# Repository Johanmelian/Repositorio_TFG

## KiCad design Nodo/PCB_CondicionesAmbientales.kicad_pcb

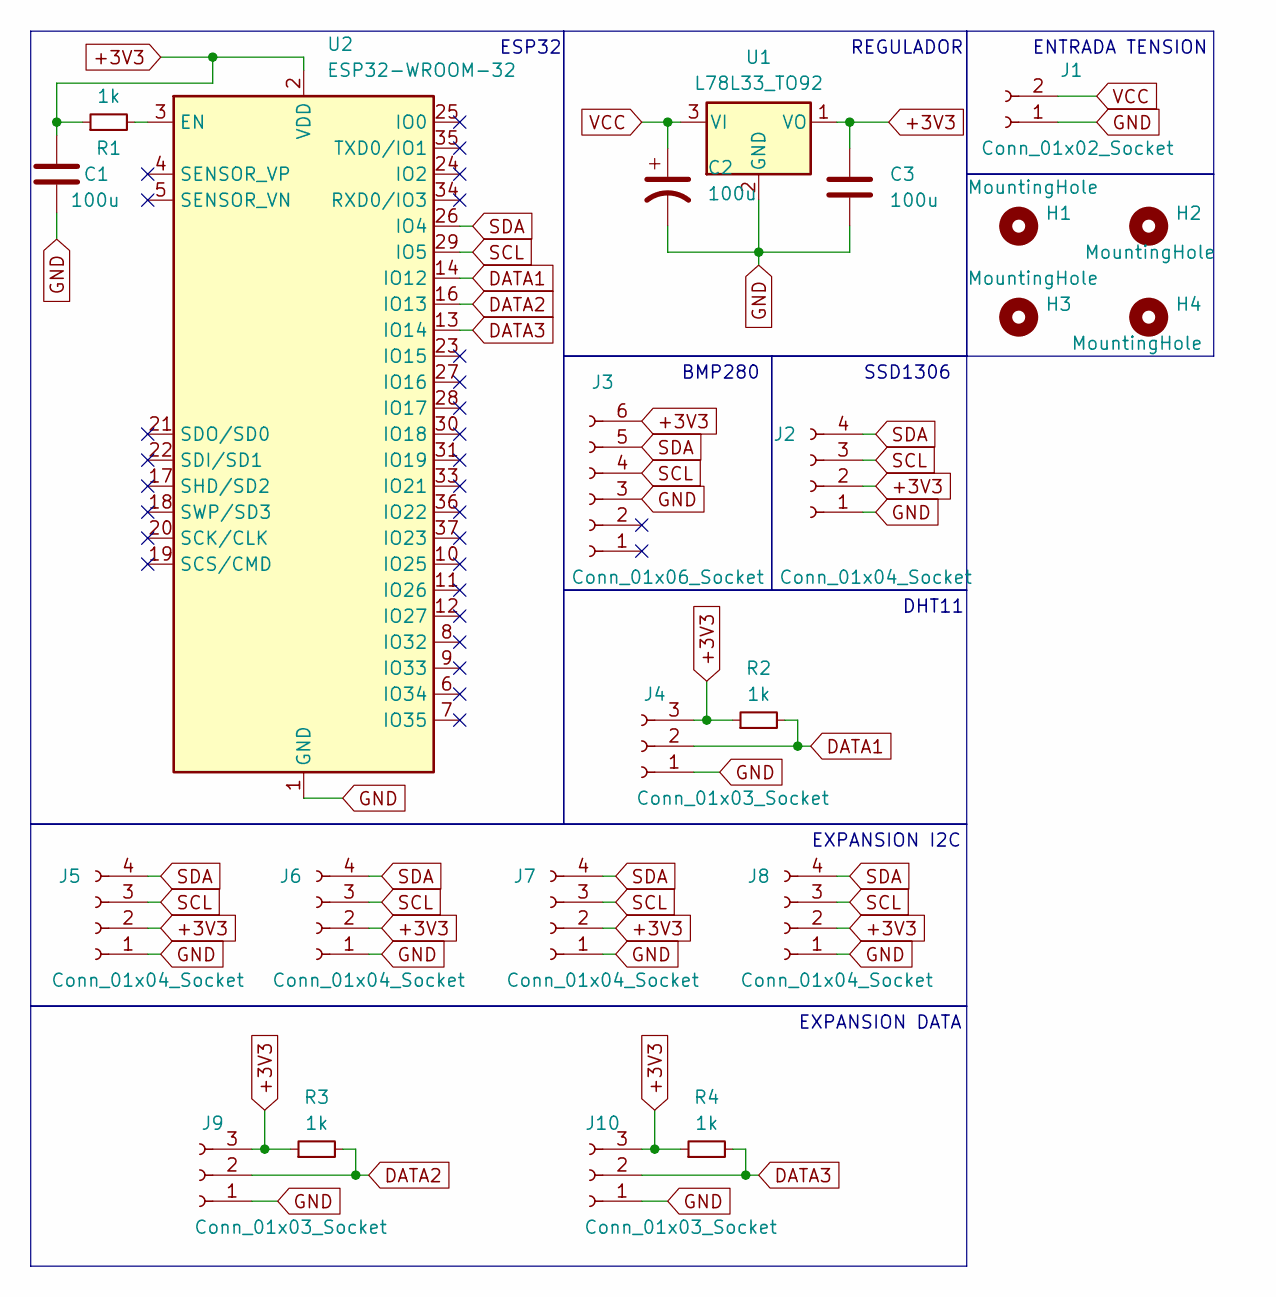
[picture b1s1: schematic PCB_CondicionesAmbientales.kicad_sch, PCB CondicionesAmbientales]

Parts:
C1, C2, C3: 100u; C_Radial_D6.3mm_H5.0mm_P2.50mm
H1, H2, H3, H4: MountingHole; MountingHole_2.5mm
J1: Conn_01x02_Socket; PinSocket_1x02_P2.54mm_Vertical
J2, J5, J6, J7, J8: Conn_01x04_Socket; PinSocket_1x04_P2.54mm_Vertical
J3: Conn_01x06_Socket; PinSocket_1x06_P2.54mm_Vertical
J4, J9, J10: Conn_01x03_Socket; PinSocket_1x03_P2.54mm_Vertical
R1, R2, R3, R4: 1k; R_Axial_DIN0204_L3.6mm_D1.6mm_P7.62mm_Horizontal
U1: L78L33_TO92; TO-92_Inline
U2: ESP32-WROOM-32

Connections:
+3V3: C1.1, C3.1, J2.2, J3.6, J4.3, J5.2, J6.2, J7.2, J8.2, J9.3, J10.3, R1.1, R2.1, R3.1, R4.1, U1.1 (VO), U2.2 (VDD)
DATA1: J4.2, R2.2, U2.14 (IO12)
DATA2: J9.2, R3.2, U2.16 (IO13)
DATA3: J10.2, R4.2, U2.13 (IO14)
GND: C1.2, C2.2, C3.2, J1.1, J2.1, J3.3, J4.1, J5.1, J6.1, J7.1, J8.1, J9.1, J10.1, U1.2 (GND), U2.1 (GND), U2.15 (GND), U2.38 (GND), U2.39 (GND)
unnamed: R1.2, U2.3 (EN)
SCL: J2.3, J3.4, J5.3, J6.3, J7.3, J8.3, U2.29 (IO5)
SDA: J2.4, J3.5, J5.4, J6.4, J7.4, J8.4, U2.26 (IO4)
VCC: C2.1, J1.2, U1.3 (VI)

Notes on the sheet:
BMP280
ESP32
REGULADOR
EXPANSION DATA
SSD1306
ENTRADA TENSION
DHT11
EXPANSION I2C

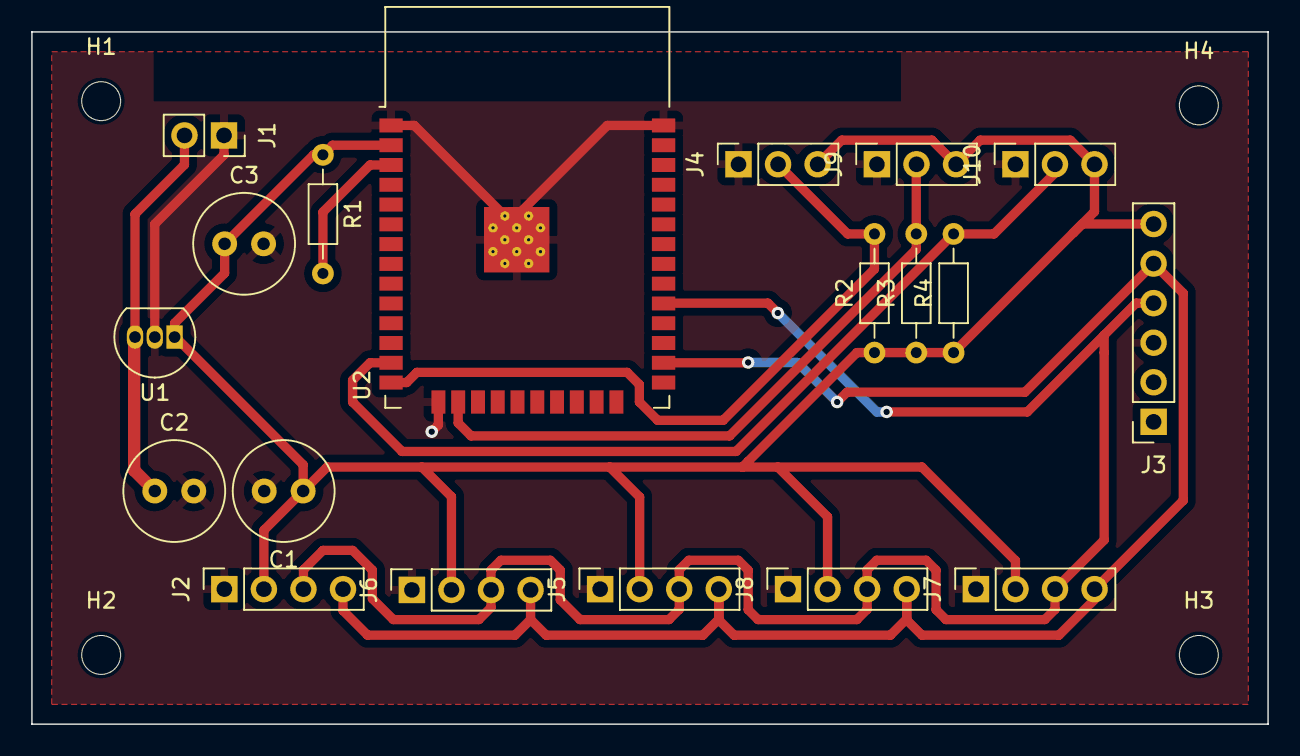
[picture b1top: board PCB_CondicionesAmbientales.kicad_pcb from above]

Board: 2 copper layers, 79.4 x 44.4 mm, 23 parts (0 on the bottom side), 9 nets.

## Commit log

2024-05-30 Creacion repo con aia de los proyectos
2024-05-31 AIAs y APKs
2024-05-31 correccion
2024-06-03 Cambios App Mantenimiento Maquinaria
2024-06-12 Actualizacion AIAs
2024-06-12 Actualizacion APKs
2024-06-17 Carpeta nodo montaje condiciones ambientales
